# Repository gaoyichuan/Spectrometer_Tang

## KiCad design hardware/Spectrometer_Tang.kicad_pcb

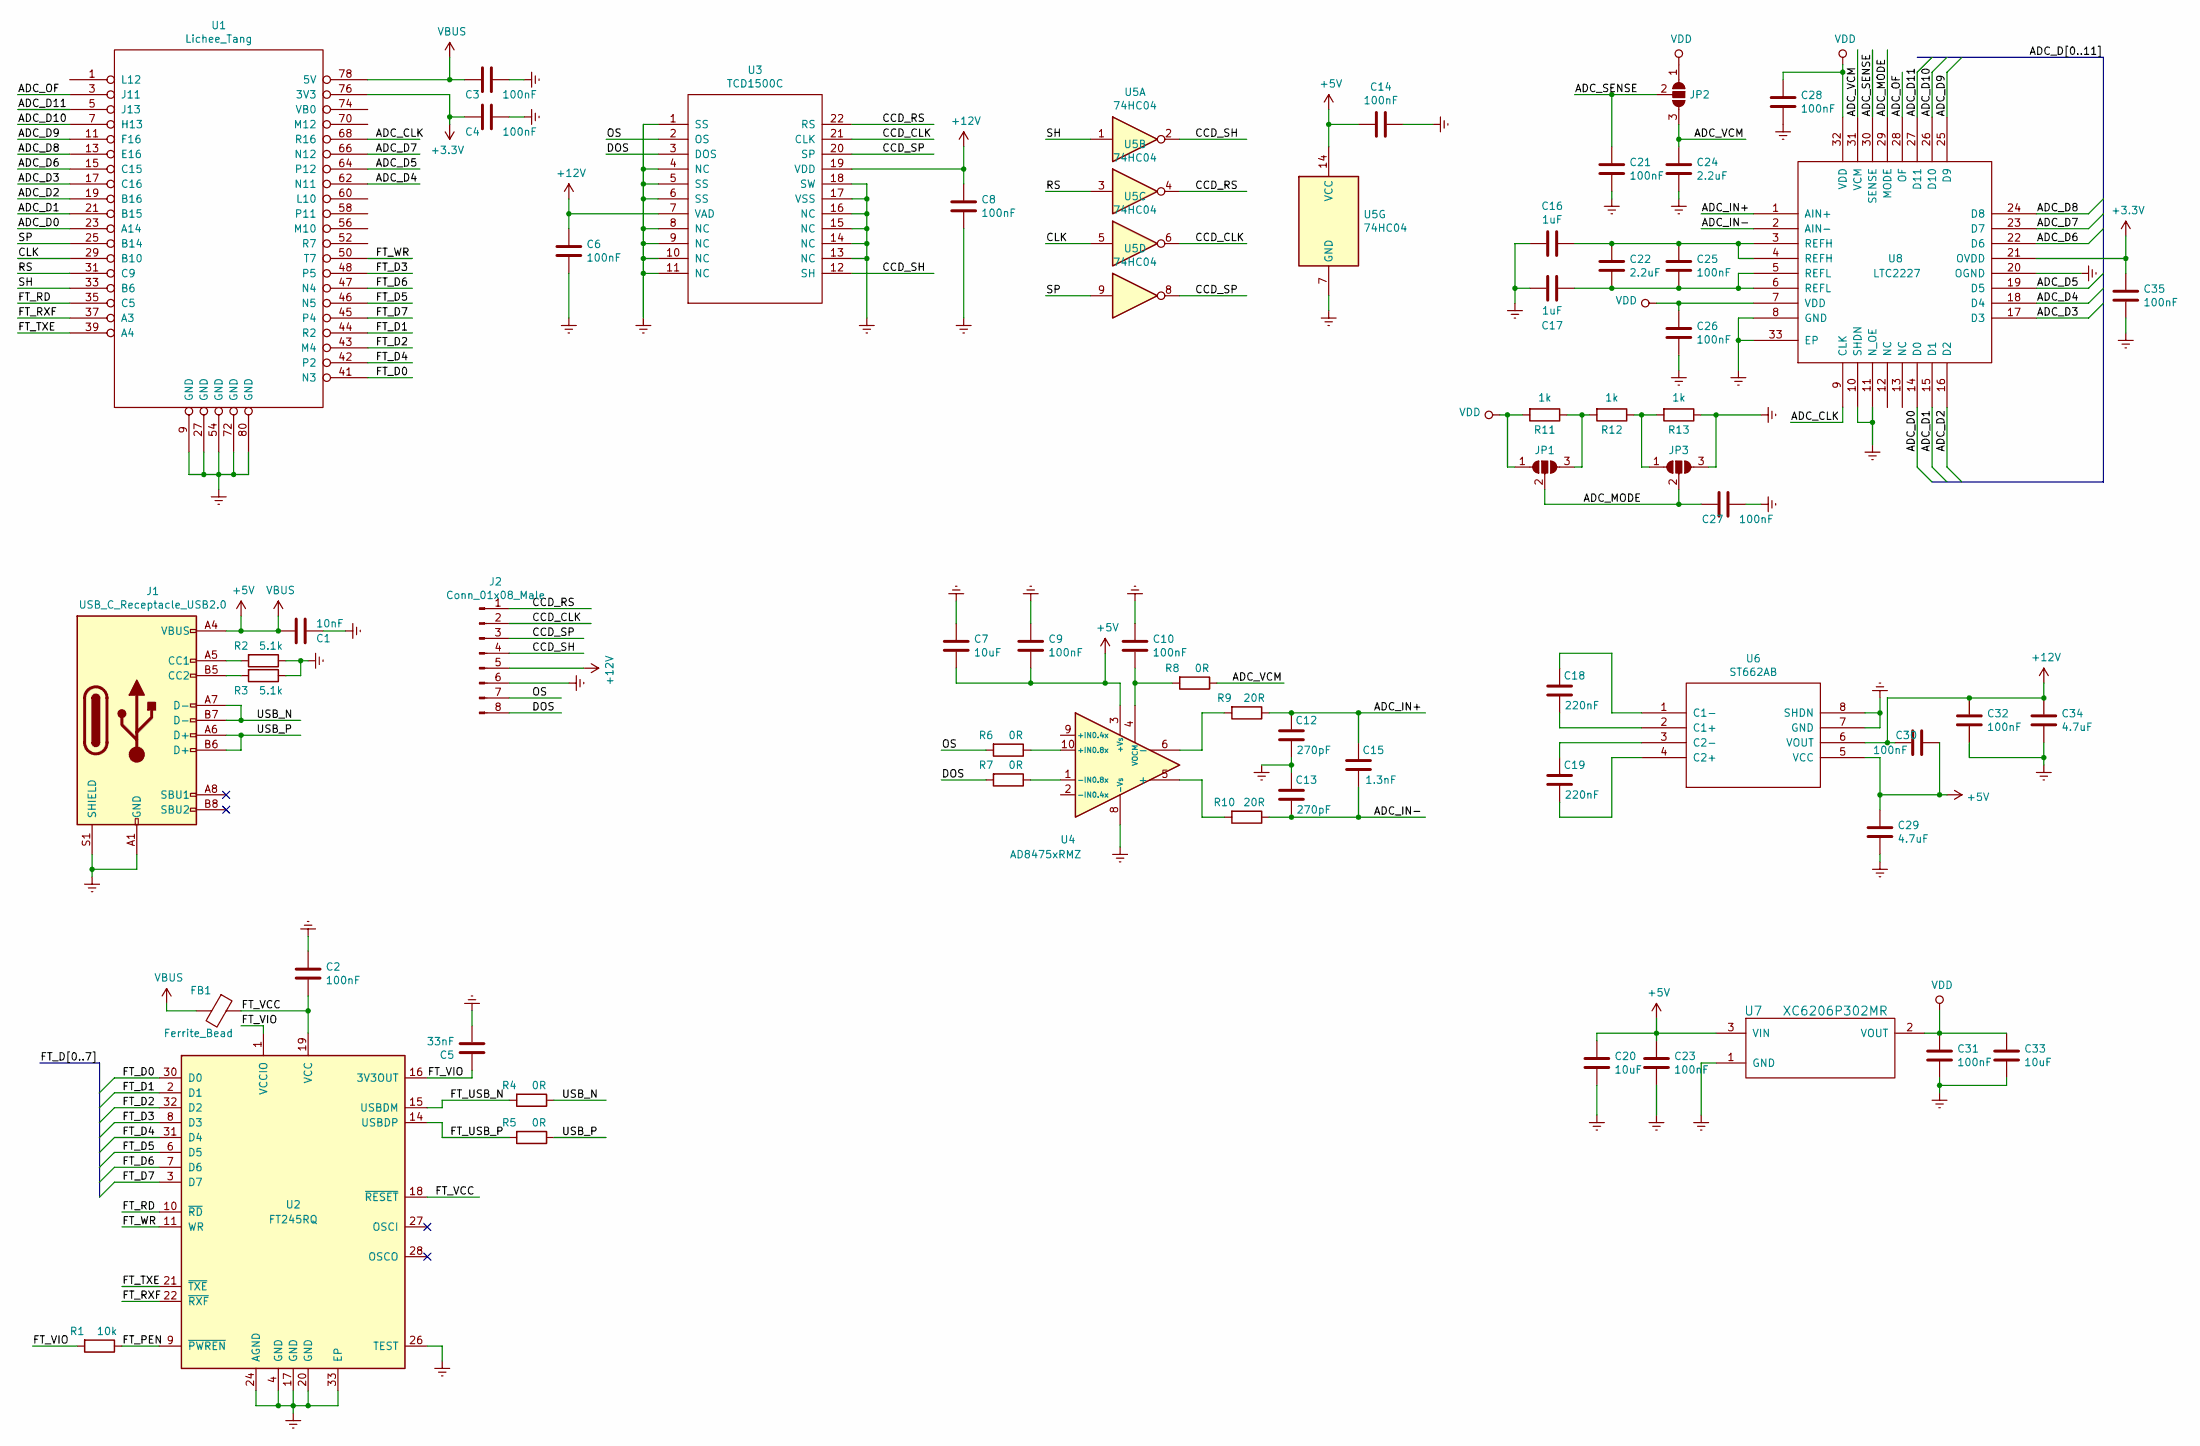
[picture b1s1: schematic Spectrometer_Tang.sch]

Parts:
C1: 10nF; C_0603_1608Metric_Pad1.05x0.95mm_HandSolder
C2, C3, C4, C6, C8, C9, C10, C14, C21, C23, C25, C26, C27, C28, C30, C31, C32, C35: 100nF; C_0603_1608Metric_Pad1.05x0.95mm_HandSolder
C5: 33nF; C_0603_1608Metric_Pad1.05x0.95mm_HandSolder
C7, C20, C33: 10uF; C_0603_1608Metric_Pad1.05x0.95mm_HandSolder
C12, C13: 270pF; C_0603_1608Metric_Pad1.05x0.95mm_HandSolder
C15: 1.3nF; C_0603_1608Metric_Pad1.05x0.95mm_HandSolder
C16, C17: 1uF; C_0603_1608Metric_Pad1.05x0.95mm_HandSolder
C18, C19: 220nF; C_0603_1608Metric_Pad1.05x0.95mm_HandSolder
C22, C24: 2.2uF; C_0603_1608Metric_Pad1.05x0.95mm_HandSolder
C29, C34: 4.7uF; C_0805_2012Metric
FB1: Ferrite_Bead; R_0603_1608Metric
J1: USB_C_Receptacle_USB2.0; USB_C_Receptacle_HRO_TYPE-C-31-M-12
J2: Conn_01x08_Male; PinHeader_1x08_P2.54mm_Vertical
JP1, JP2, JP3: SolderJumper_3_Open; SolderJumper-3_P1.3mm_Open_RoundedPad1.0x1.5mm
R1: 10k; R_0603_1608Metric_Pad1.05x0.95mm_HandSolder
R2, R3: 5.1k; R_0603_1608Metric_Pad1.05x0.95mm_HandSolder
R4, R5, R6, R7, R8: 0R; R_0603_1608Metric_Pad1.05x0.95mm_HandSolder
R9, R10: 20R; R_0603_1608Metric_Pad1.05x0.95mm_HandSolder
R11, R12, R13: 1k; R_0603_1608Metric_Pad1.05x0.95mm_HandSolder
U1: Lichee_Tang; Lichee-Tang-Module
U2: FT245RQ; QFN-32-1EP_5x5mm_P0.5mm_EP3.45x3.45mm_ThermalVias
U3: TCD1500C
U4: AD8475xRMZ; MSOP-10_3x3mm_P0.5mm
U5: 74HC04
U6: ST662AB; SO-8_3.9x4.9mm_P1.27mm
U7: XC6206P302MR; SOT-23
U8: LTC2227; QFN-32-1EP_5x5mm_P0.5mm_EP3.45x3.45mm_ThermalVias

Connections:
+3V3: C4.2, C35.1, U1.76 (3V3), U8.21 (OVDD)
+5V: C1.2, C3.2, C7.2, C9.2, C14.2, C20.1, C23.1, C29.1, C30.1, FB1.2, J1.A4 (VBUS), J1.A9 (VBUS), J1.B4 (VBUS), J1.B9 (VBUS), U1.78 (5V), U4.3 (+Vs), U5.14 (VCC), U6.5 (VCC), U7.3 (VIN)
+12V: C6.1, C8.1, C30.2, C32.1, C34.1, J2.5, U3.7 (VAD), U3.19 (VDD), U6.6 (VOUT)
/ADC_CLK: U1.68 (R16), U8.9 (CLK)
/ADC_D0: U1.23 (A14), U8.14 (D0)
/ADC_D1: U1.21 (B15), U8.15 (D1)
/ADC_D2: U1.19 (B16), U8.16 (D2)
/ADC_D3: U1.17 (C16), U8.17 (D3)
/ADC_D4: U1.62 (N11), U8.18 (D4)
/ADC_D5: U1.64 (P12), U8.19 (D5)
/ADC_D6: U1.15 (C15), U8.22 (D6)
/ADC_D7: U1.66 (N12), U8.23 (D7)
/ADC_D8: U1.13 (E16), U8.24 (D8)
/ADC_D9: U1.11 (F16), U8.25 (D9)
/ADC_D10: U1.7 (H13), U8.26 (D10)
/ADC_D11: U1.5 (J13), U8.27 (D11)
/ADC_IN+: C12.2, C15.2, R9.1, U8.1 (AIN+)
/ADC_IN-: C13.1, C15.1, R10.1, U8.2 (AIN-)
/ADC_MODE: C27.2, JP1.2 (C), JP3.2 (C), U8.29 (MODE)
/ADC_OF: U1.3 (J11), U8.28 (OF)
/ADC_SENSE: C21.1, JP2.2 (C), U8.30 (SENSE)
/ADC_VCM: C24.1, JP2.3 (B), R8.1, U8.31 (VCM)
/CCD_CLK: J2.2, U3.21 (CLK), U5.6
/CCD_RS: J2.1, U3.22 (RS), U5.4
/CCD_SH: J2.4, U3.12 (SH), U5.2
/CCD_SP: J2.3, U3.20 (SP), U5.8
/CLK: U1.29 (B10), U5.5
/DOS: J2.8, R7.2, U3.3 (DOS)
/FT_D0: U1.41 (N3), U2.30 (D0)
/FT_D1: U1.44 (R2), U2.2 (D1)
/FT_D2: U1.43 (M4), U2.32 (D2)
/FT_D3: U1.48 (P5), U2.8 (D3)
/FT_D4: U1.42 (P2), U2.31 (D4)
/FT_D5: U1.46 (N5), U2.6 (D5)
/FT_D6: U1.47 (N4), U2.7 (D6)
/FT_D7: U1.45 (P4), U2.3 (D7)
/FT_PEN: R1.1, U2.9 (~PWREN)
/FT_RD: U1.35 (C5), U2.10 (~RD)
/FT_RXF: U1.37 (A3), U2.22 (~RXF)
/FT_TXE: U1.39 (A4), U2.21 (~TXE)
/FT_USB_N: R4.2, U2.15 (USBDM)
/FT_USB_P: R5.2, U2.14 (USBDP)
/FT_VCC: C2.2, FB1.1, U2.18 (~RESET), U2.19 (VCC)
/FT_VIO: C5.1, R1.2, U2.1 (VCCIO), U2.16 (3V3OUT)
/FT_WR: U1.50 (T7), U2.11 (WR)
/OS: J2.7, R6.2, U3.2 (OS)
/RS: U1.31 (C9), U5.3
/SH: U1.33 (B6), U5.1
/SP: U1.25 (B14), U5.9
/USB_N: J1.A7 (D-), J1.B7 (D-), R4.1
/USB_P: J1.A6 (D+), J1.B6 (D+), R5.1
Earth: C1.1, C2.1, C3.1, C4.1, C5.2, C6.2, C7.1, C8.2, C9.1, C10.1, C12.1, C13.2, C14.1, C16.2, C17.2, C20.2, C21.2, C23.2, C24.2, C26.2, C27.1, C28.2, C29.2, C31.2, C32.2, C33.2, C34.2, C35.2, J1.A1 (GND), J1.A12 (GND), J1.B1 (GND), J1.B12 (GND), J1.S1 (SHIELD), J2.6, JP3.3 (B), R2.1, R3.1, R13.1, U1.9 (GND), U1.27 (GND), U1.54 (GND), U1.72 (GND), U1.80 (GND), U2.4 (GND), U2.17 (GND), U2.20 (GND), U2.24 (AGND), U2.26 (TEST), U2.33 (EP), U3.1 (SS), U3.4 (NC), U3.5 (SS), U3.6 (SS), U3.8 (NC), U3.9 (NC), U3.10 (NC), U3.11 (NC), U3.13 (NC), U3.14 (NC), U3.15 (NC), U3.16 (NC), U3.17 (VSS), U3.18 (SW), U4.8 (-Vs), U5.7 (GND), U6.7 (GND), U6.8 (SHDN), U7.1 (GND), U8.8 (GND), U8.10 (SHDN), U8.11 (N_OE), U8.20 (OGND), U8.33 (EP)
unnamed: C10.2, R8.2, U4.4 (VOCM)
unnamed: C16.1, C22.1, C25.1, U8.3 (REFH), U8.4 (REFH)
unnamed: C17.1, C22.2, C25.2, U8.5 (REFL), U8.6 (REFL)
unnamed: C18.1, U6.2 (C1+)
unnamed: C18.2, U6.1 (C1-)
unnamed: C19.1, U6.4 (C2+)
unnamed: C19.2, U6.3 (C2-)
unnamed: J1.A5 (CC1), R2.2
unnamed: J1.B5 (CC2), R3.2
unnamed: JP1.3 (B), R11.1, R12.2
unnamed: JP3.1 (A), R12.1, R13.2
unnamed: R6.1, U4.10 (+IN0.8x)
unnamed: R7.1, U4.1 (-IN0.8x)
unnamed: R9.2, U4.6 (-)
unnamed: R10.2, U4.5 (+)
VDD: C26.1, C28.1, C31.1, C33.1, JP1.1 (A), JP2.1 (A), R11.2, U7.2 (VOUT), U8.7 (VDD), U8.32 (VDD)

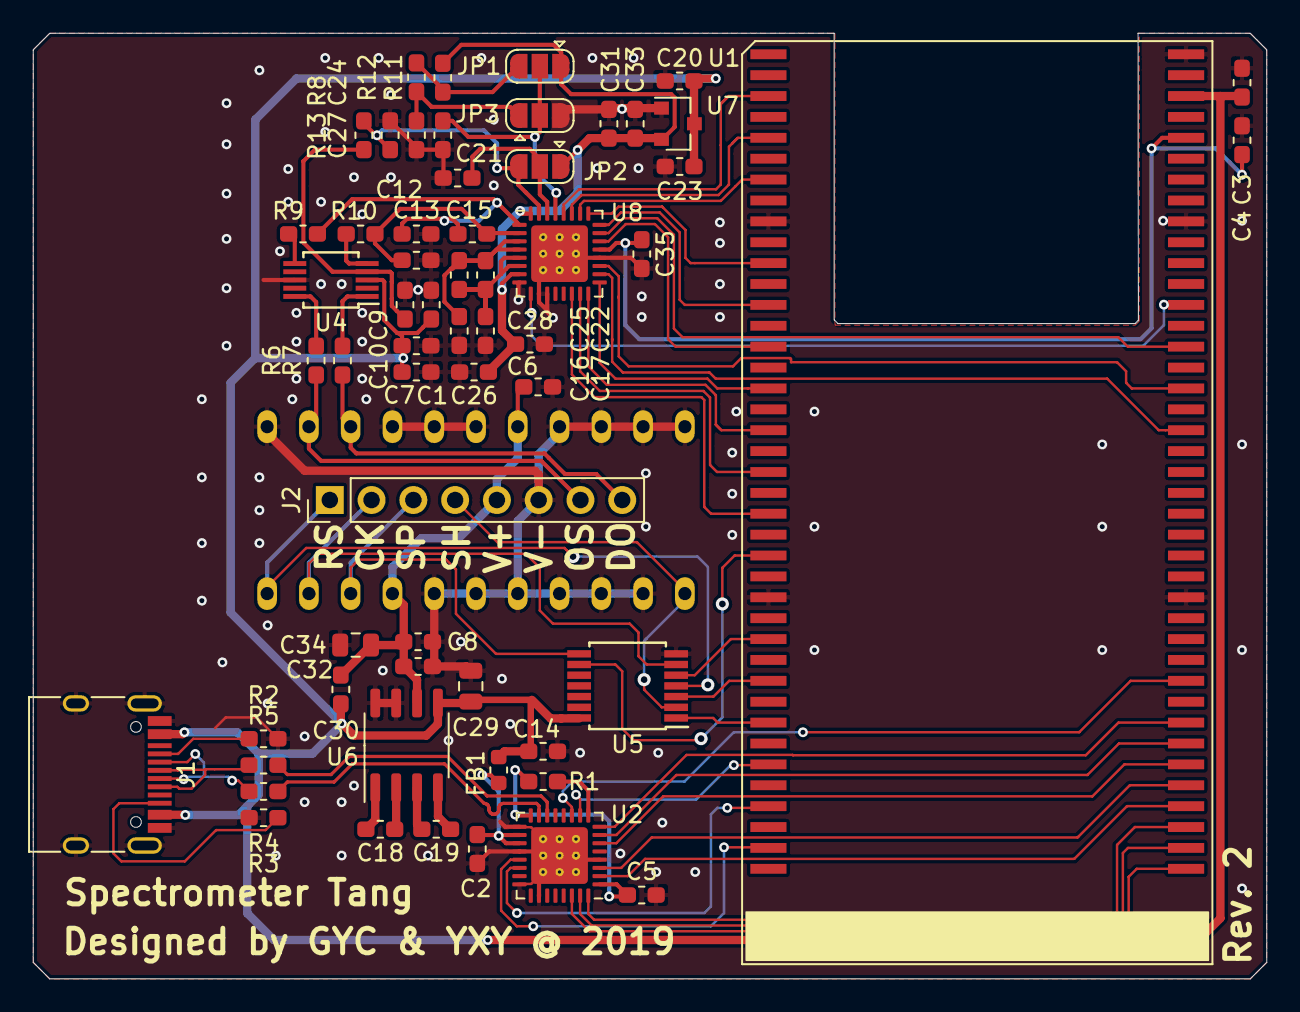
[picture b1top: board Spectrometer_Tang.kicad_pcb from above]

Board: 2 copper layers, 75.0 x 57.5 mm, 61 parts (1 on the bottom side), 68 nets.

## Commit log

2019-05-02 Add some documents
2019-05-02 Some style fix
2019-05-02 Add gitignore
2019-05-02 initial version
2019-05-02 working ccd driver
2019-05-02 change adc filename to ltc2227
2019-05-02 update io constraint for ADC pins
2019-05-02 update gitignore for td log files
2019-05-02 add FT245 doc
2019-05-22 Rewrite CCD driver
    temp version
    part code
    temp commit
    work version
    update gitignore
2019-06-28 Add Qt GUI
2019-06-28 Add mechinal files
2019-06-28 Use 0xF5AA as start mark
2019-11-11 Fix level converter & usb port location
